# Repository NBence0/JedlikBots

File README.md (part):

# JedlikBots – Future Robotics Engineers from Győr, Hungary

Welcome to the official GitHub page of **JedlikBots**! 🎓🤖 We are the dedicated team of software development and robotics students from the Jedlik Ányos Technical School in Győr, Hungary. Our passion is to combine mechanical engineering, electronics, and software development to create innovative robotics solutions that address real-world problems. Our goal is to apply our acquired knowledge in national and international competitions and to inspire the next generation of engineers.

---

## 🚀 Our Main Project: ProBot X1 – The Next Generation of Competition Robots

The **ProBot X1** is our team's flagship project: a professional, modular robot platform specifically designed for the **WRO (World Robot Olympiad)** international competition series and other high-level technological challenges. During the robot's development, we use state-of-the-art technologies to create a truly competitive and versatile device.

<p align="center">
  
  <br>
  <em>The early but functional prototype of the ProBot X1 in its development environment.</em>
</p>

---

## 🔧 Technical Deep Dive: The Anatomy of ProBot X1

The ProBot X1 is not just a robot—it's a complex system designed and built with precision engineering. Below, we provide a detailed overview of the project's technical background.

### 1. Mechanical Design and Manufacturing Philosophy

The robot's physical frame and all mechanical components are entirely custom-designed. Our design philosophy centers around **modularity**, **robustness**, and **rapid iteration**.

*   **Design Software:** We create our models in professional CAD software, where every component is designed down to the smallest detail.
*   **Manufacturing Technology:** The parts are produced using 3D printing. This allows us to test new prototypes within days and flexibly adapt the robot's structure to the specific requirements of a given competition task.
*   **Material Selection:** We use PLA for prototypes and PETG or ABS for the final, high-stress components to ensure adequate strength and durability.

| Design in CAD Software (Video) | The Finished, Printed Components |
| :-------------------------------------------------------------------------------------------------------------------------------------------------------------------: | :-----------------------------------------------------------------------------------------------------------------: |
|  |  |
<p align="center"><em>On the left, the design process (click for video!), and on the right, the finished, printed components next to measurement instruments. The lattice structure provides optimal rigidity with minimal weight.</em></p>

### 2. Advanced Electronics and Custom-Designed PCB

The robot's brain and nervous system are comprised of a custom Printed Circuit Board (PCB) designed by us, located in the `Circuit/kicad/Robot fő nyák_v3/` folder. Our goal was to create a central board that integrates all control and sensor functions, minimizing wiring and maximizing reliability.

**The main functional blocks of the PCB:**

*   **Central Processing Unit (CPU):** The board hosts a **Raspberry Pi Compute Module 5 (CM5)**, which is responsible for computationally intensive tasks like machine vision and artificial intelligence.
*   **Real-Time Microcontroller (MCU):** An **ESP32-S3** microcontroller handles low-level, hardware-related control (motors, sensors), guaranteeing deterministic, real-time operation.
*   **Motor Control Subsystem:**
    *   Four **TMC5160** stepper motor drivers controlled via SPI for precise and silent movement. These drivers have advanced features like `StealthChop2™` for silent operation and `StallGuard2™` for sensorless homing.
    *   Multiple H-bridge outputs for driving DC motors and other actuators.
*   **Power Supply Unit (PSU):** A complex power supply providing multiple voltage levels (5V, 12V) and managing battery charging (`Battery-circuit.kicad_sch`). The system monitors the battery status and provides protection against overcharging and deep discharge.
*   **Sensor Interfaces:**
    *   **I²C Bus:** Multiple I²C devices, including a 9-axis IMU (BNO085) and an environmental sensor (BME280), are connected through an I²C multiplexer, allowing the simultaneous use of devices with the same address.
    *   **Analog-to-Digital Converter (ADC):** A high-resolution ADC (`ADS8688`) is responsible for the precise digitization of analog sensor signals (e.g., distance sensors).
*   **Peripherals:** USB hub, SD card reader, and numerous GPIO pins for modular expandability.

<p align="center">
  
  <br>
  <em>The "cable jungle"—an essential part of the prototyping phase, from which the final, clean PCB is born.</em>
</p>

### 3. Software Architecture and Intelligent Control

Hardware is only as good as the software that runs on it. The ProBot X1 is built on a sophisticated, two-tier software architecture.

#### High-Level Control (Raspberry Pi - Python)
The Python environment running on the Raspberry Pi is responsible for the robot's "intelligence."

*   **Machine Vision (OpenCV):** Our code in the `Camera/` folder implements a complete image processing pipeline:
    1.  **Image Acquisition:** Reading the frame from the camera.
    2.  **Preprocessing:** Converting the image to the HSV color space, which is more resistant to changes in lighting conditions. Applying Gaussian blur to reduce noise.
    3.  **Color and Shape Recognition:** Identifying relevant objects (e.g., colored blocks, lines) using color masking and contour detection.
    4.  **Data Extraction:** Determining the position, size, and orientation of objects in the camera's view.
*   **Decision-Making and Strategy:** Based on the processed data, the robot builds a state-space representation of its environment and plans its next moves to optimize score.

<p align="center">
  
  <br>
  <em>Click the image to watch the video! Based on the camera's image, the LED strip connected to the ESP32 lights up with the corresponding color.</em>
</p>

#### Low-Level Control and Firmware (ESP32 - C++)
The C++ firmware running on the ESP32 microcontroller, developed in the `PlatformIO` environment, ensures hard real-time operation.

*   **Responsibilities:** Receiving commands from the Raspberry Pi, precise stepping of motors, continuous collection and transmission of sensor data, and critical fault handling.
*   **Communication Protocol:** A custom, packet-based UART protocol connects the two brains. The protocol, developed in our `robot modells/v1.0/Full_uart_communication_logic_v2/` project, has the structure: `[START_BYTE, COMMAND_ID, PAYLOAD_LENGTH, PAYLOAD..., CHECKSUM]`. This structure guarantees data integrity and robust operation.

---

## 👥 Our Team

Meet the driving force behind JedlikBots, the students who power the project:

| Photo | Name | Role & Expertise |
| :---: | :--- | :--- |
|  | **Bence Nagy** | **Software Developer.** Specializes in sensor data processing, embedded systems programming, and 3D modeling. Bence is responsible for the robot's hardware abstraction layer and the design of its mechanical components. |
|  | **Nándor Schmidt** | **Electronics Designer & Firmware Developer.** The expert on the embedded systems behind the robots' "brains." He designs the PCBs and writes the low-level firmware, ensuring a perfect harmony between hardware and software. |
|  | **Bálint Buda** | **AI & Communications Developer.** Bálint is responsible for implementing machine learning algorithms and for the robot's wired and wireless communication. |

---

## 🏆 Competition Results and Goals

We are proud of our achievements so far and have set even bigger goals for ourselves.

*   **🥈 WRO 2025 Regional Final, Budapest - 2nd Place (May 2025)**
    *   We entered our first WRO competition with a LEGO Mindstorms EV3-based robot and achieved 2nd place in the Budapest regional final. This success qualified us for the national final but also highlighted the limitations of our current technology. With the new, professional ProBot X1, our goal is the World Final!

<p align="center">
  
  <br>
  <em>Click the image to watch our LEGO robot's competition run!</em>
</p>

---

## ❤️ Support the Engineers of the Future!

Developing the ProBot X1 and participating in international competitions require significant financial and technical resources. Our goal is to perform well at the WRO World Final, which requires building a world-class robot. This is where we need your help!

<p align="center">
  
  <br>
  <em>Click the image to see our workshop in action! This is where ideas and robots are born.</em>
</p>

### How You Can Help

1.  **With Equipment:** Modern components are essential for our project. Every single piece of donated equipment is a huge help. What we need most:
    *   **Microcontrollers:** Raspberry Pi (any version, including Compute Modules), STM-based boards.
    *   **Motors and Controllers:** Stepper motors, DC motors, servos, motor controllers.
    *   **Sensors:** Precision color and distance sensors, camera modules.
    *   **Materials:** 3D printer filament (PLA, PETG, 1.75 mm), breadboards, cables.
    *   **Measurement Tools:** Logic analyzer for debugging, oscilloscope.

2.  **With Professional Mentorship:** If you are an experienced engineer or developer and would like to share your knowledge, please contact us! A piece of good advice can be invaluable.

3.  **With Financial Support:** Your financial contribution can directly support the purchase of components and our travel to competitions.
### Contact
If you would like to contribute to our success, please write to us!
*   **Email:** nagy.bence1@students.jedlik.eu
*   **Phone:** +36 30 368 8136

---

## 🙏 Our Sponsors

We are deeply grateful to our current sponsors who believe in us and support our work!

<p align="center">

</p>

---

## 📂 Repository Contents

This repository documents the entire work of the JedlikBots team. You can find our projects in the following folders:

*   **`/Circuit/`**: Contains the designs for our custom Printed Circuit Boards (PCBs) in KiCad and Altium formats.
*   **`/Robot 3d/`**: 3D models of the robot's mechanical parts (STL, STP files).
*   **`/robot modells/`**: Various software modules and experimental programs that implement the robot's functions (PlatformIO projects).
*   **`/Camera/`**: Python scripts related to machine vision.
*   **`/media/`**: Images and videos of the robot, the team, and the competitions.
*   **`/web/`**: The source code for the team's official website.

**Thank you for your time! Follow our work and cheer for us at the next competition!**
# JedlikBots – A Jövő Robotikai Mérnökei Győrből

---
---

Üdvözlünk a **JedlikBots** hivatalos GitHub oldalán! 🎓🤖 Mi vagyunk a Győri Jedlik Ányos Technikum szoftverfejlesztő és robotika iránt elkötelezett diákcsapata. Szenvedélyünk a gépészet, az elektronika és a szoftverfejlesztés ötvözése, amellyel innovatív, valós problémákra választ adó robotikai megoldásokat hozunk létre. Célunk, hogy a megszerzett tudást hazai és nemzetközi versenyeken kamatoztassuk, és inspiráljuk a jövő mérnökgenerációját.

---

## 🚀 Fő Projektünk: ProBot X1 – A Versenyrobot Új Generációja

A **ProBot X1** a csapatunk zászlóshajója: egy professzionális, moduláris robotplatform, amelyet kifejezetten a **WRO (World Robot Olympiad)** nemzetközi versenysorozatra, valamint más magas szintű technológiai kihívásokra terveztünk. A robot fejlesztése során a legmodernebb technológiákat alkalmazzuk, hogy egy valóban versenyképes és sokoldalú eszközt hozzunk létre.

<p align="center">
  
  <br>
  <em>A ProBot X1 korai, de működő prototípusa a fejlesztői környezetben.</em>
</p>

---

## 🔧 Technikai Mélymerülés: A ProBot X1 Anatómája

A ProBot X1 nem csupán egy robot – egy komplex, precíziós mérnöki munkával megtervezett és épített rendszer. Az alábbiakban részletesen bemutatjuk a projekt műszaki hátterét.

### 1. Mechanikai Tervezés és Gyártásfilozófia

A robot fizikai váza és minden mechanikai eleme teljes mértékben egyedi tervezésű. A tervezési filozófiánk középpontjában a **modularitás**, a **robusztusság** és a **gyors iterálhatóság** áll.

*   **Tervező Szoftver:** A modelleket professzionális CAD szoftverekben készítjük, ahol minden alkatrészt a legapróbb részletekig megtervezünk.
*   **Gyártástechnológia:** Az alkatrészeket 3D nyomtatással állítjuk elő. Ez lehetővé teszi, hogy napok alatt új prototípusokat teszteljünk, és a robotot rugalmasan az adott versenyfeladat specifikus igényeihez igazítsuk.
*   **Anyagválasztás:** A prototípusokhoz PLA-t, a végleges, nagy igénybevételnek kitett alkatrészekhez pedig PETG-t vagy ABS-t használunk a megfelelő szilárdság és tartósság érdekében.

| Tervezés a CAD Szoftverben (Videó) | A Kész, Nyomtatott Alkatrészek |
| :-------------------------------------------------------------------------------------------------------------------------------------------------------------------: | :-----------------------------------------------------------------------------------------------------------------: |
|  |  |
<p align="center"><em>Bal oldalon a tervezési folyamat (kattints a videóért!), jobb oldalon a kész, nyomtatott alkatrészek a mérőműszerek mellett. A rácsszerkezet optimális merevséget biztosít minimális súly mellett.</em></p>

### 2. Fejlett Elektronika és Egyedi Tervezésű NyÁK

A robot agyát és idegrendszerét egy általunk, a `Circuit/kicad/Robot fő nyák_v3/` mappában tervezett egyedi nyomtatott áramkör (PCB) alkotja. A célunk egy olyan központi panel létrehozása volt, amely integrálja az összes vezérlési és szenzorikai funkciót, minimalizálva a kábelezést és maximalizálva a megbízhatóságot.

**A NyÁK fő funkcionális blokkjai:**

*   **Központi Feldolgozó Egység (CPU):** A panel fogad egy **Raspberry Pi Compute Module 5 (CM5)** kártyát, amely a nagy számítási igényű feladatokért, mint a gépi látás és a mesterséges intelligencia, felel.
*   **Valós Idejű Mikrokontroller (MCU):** Egy **ESP32-S3** mikrokontroller végzi a hardverközeli, alacsony szintű vezérlést (motorok, szenzorok), garantálva a determinisztikus, valós idejű működést.
*   **Motorvezérlő Alrendszer:**
    *   4 darab, SPI-on keresztül vezérelt **TMC5160** léptetőmotor-meghajtó a precíz és csendes mozgásért. Ezen meghajtók olyan fejlett funkciókkal bírnak, mint a `StealthChop2™` a hangtalan működésért és a `StallGuard2™` a szenzor nélküli végállás-érzékelésért.
    *   Több, H-híddal ellátott kimenet DC motorok és egyéb aktuátorok meghajtásához.
*   **Energiaellátás (PSU):** Egy komplex, több feszültségszintet (5V, 12V) biztosító tápegység, amely az akkumulátor töltését is menedzseli (`Battery-circuit.kicad_sch`). A rendszer figyeli az akkumulátor állapotát, és védelmet nyújt a túltöltés és mélykisülés ellen.
*   **Szenzor Interfészek:**
    *   **I²C Busz:** Több I²C eszköz, köztük egy 9 tengelyes IMU (BNO085) és egy környezeti szenzor (BME280) csatlakozik egy I²C multiplexeren keresztül, amely lehetővé teszi az azonos című eszközök egyidejű használatát.
    *   **Analóg-Digitális Konverter (ADC):** Egy nagy felbontású ADC (`ADS8688`) felel az analóg szenzorok (pl. távolságmérők) jeleinek precíz digitalizálásáért.
*   **Perifériák:** USB hub, SD kártya olvasó, és számos GPIO kivezetés a moduláris bővíthetőség érdekében.

<p align="center">
  
  <br>
  <em>A "kábel dzsungel" – a prototípus fázis elengedhetetlen része, amelyből a végleges, letisztult PCB megszületik.</em>
</p>

### 3. Szoftver Architektúra és Intelligens Vezérlés

A hardver csak annyit ér, amennyit a szoftver kihoz belőle. A ProBot X1 egy kifinomult, kétlépcsős szoftveres architektúrára épül.

#### Magas Szintű Vezérlés (Raspberry Pi - Python)
A Raspberry Pi-on futó Python környezet felel a robot "intelligenciájáért".

*   **Gépi Látás (OpenCV):** A `Camera/` mappában található kódjaink egy komplett képfeldolgozási folyamatot valósítanak meg:
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
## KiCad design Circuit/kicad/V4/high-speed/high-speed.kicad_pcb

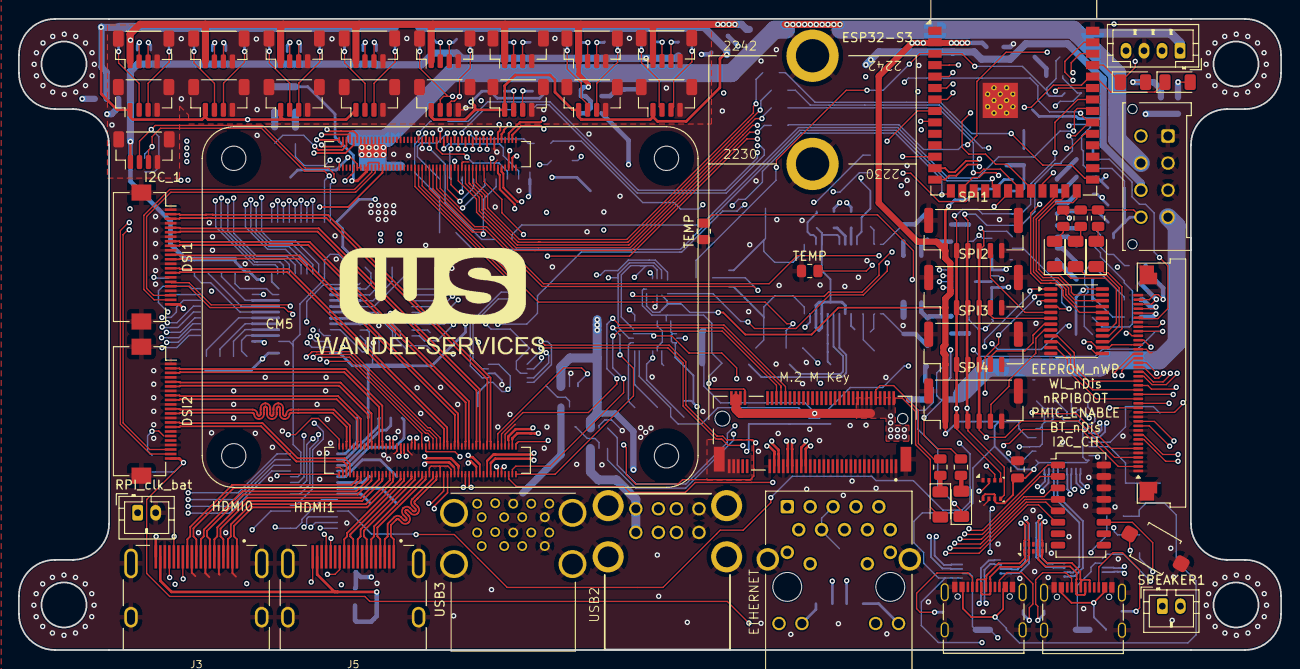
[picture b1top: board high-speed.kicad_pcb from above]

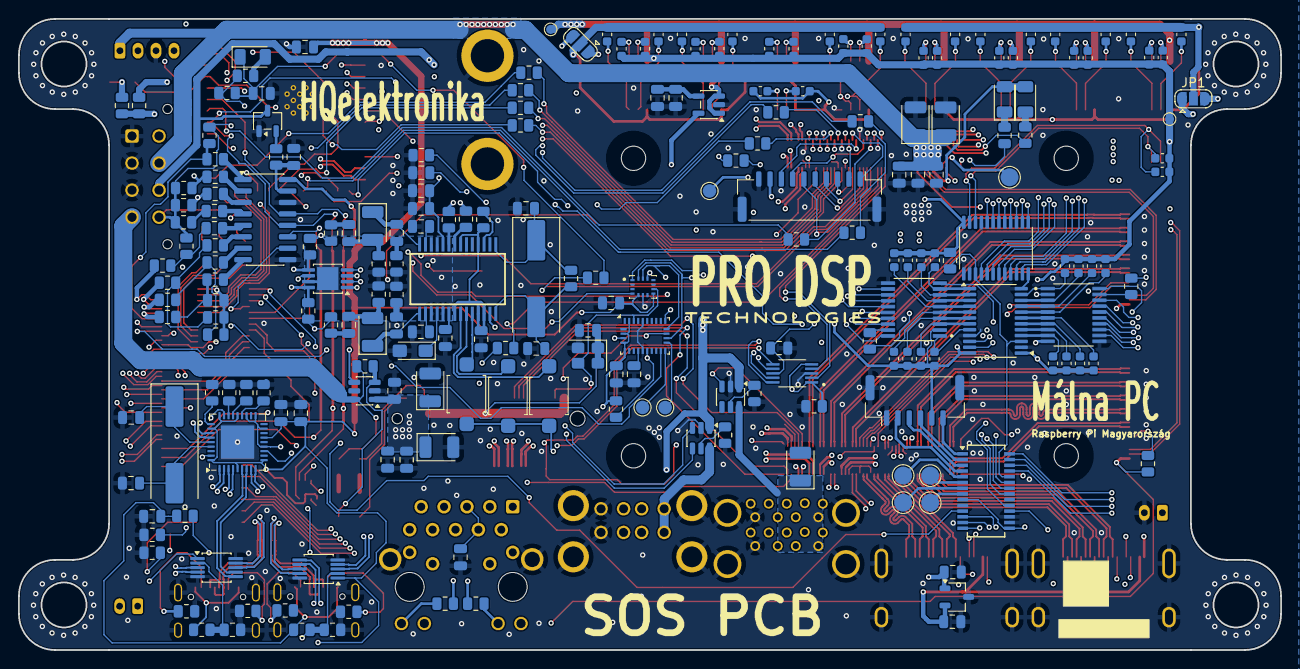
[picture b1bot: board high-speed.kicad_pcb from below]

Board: 6 copper layers, 140.0 x 70.0 mm, 274 parts (216 on the bottom side), 358 nets.

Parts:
C1, C2, C3, C7, C8, C13, C15, C18, C19, C21, C27, C36, C44, C59: 100nf; C_0805_2012Metric
C5, C6: 330pf; C_0805_2012Metric
C10, C66, C71: 100uF; CP_EIA-3528-21_Kemet-B
C14, C17, C24, C25, C28, C31, C61, C63, C64, C65, C67, C72: 1uf; C_0805_2012Metric
C16, C20, C58, C68, C69, C73: 22nf c0g; C_0805_2012Metric
C22, C23, C56, C57: 22pf; C_0805_2012Metric
C62: 10uF; CP_EIA-3216-18_Kemet-A_HandSolder
CM5: ComputeModule5-CM5; Raspberry-Pi-5-Compute-Module
CT1, CT2, CT3, CT4: 100uF; CP_EIA-3528-21_Kemet-B
D1, D2, D3, D4, D5, D6, D7, D8, D9, D10: LED; D_1206_3216Metric
DSI1: dsi; Hirose_FH12-22S-0.5SH_1x22-1MP_P0.50mm_Horizontal
DSI2: dsi1; Hirose_FH12-22S-0.5SH_1x22-1MP_P0.50mm_Horizontal
DSW1: SW_DIP_x08; SW_DIP_SPSTx08_Slide_Copal_CHS-08A_W5.08mm_P1.27mm_JPin
ESP32-S3: ESP32-S3-WROOM-1
I2C_0x70_1, I2C_0x70_2, I2C_0x70_3, I2C_0x70_4, I2C_0x70_5, I2C_0x70_6, I2C_0x70_7, I2C_0x70_8, I2C_0x71_1, I2C_0x71_2, I2C_0x71_3, I2C_0x71_4, I2C_0x71_5, I2C_0x71_6, I2C_0x71_7, I2C_0x71_8: Conn_01x04_Pin; JST_SH_BM04B-SRSS-TB_1x04-1MP_P1.00mm_Vertical
I2C_1: for default bus; JST_SH_BM04B-SRSS-TB_1x04-1MP_P1.00mm_Vertical
J1: Power Input; Molex_Micro-Fit_3.0_43045-0812_2x04_P3.00mm_Vertical
J2: from psu panel; Amphenol_F32Q-1A7x1-11040_1x40-1MP_P0.5mm_Horizontal
J3: HDMI0; EDAC 690-019-298-412
J5: HDMI1; EDAC 690-019-298-412
J6: RGB-BTN; JST_GH_BM06B-GHS-TBT_1x06-1MP_P1.25mm_Vertical
J7: MagJack-A70-112-331N126; TRJG0926HENL
J8: Fan; JST_PH_B4B-PH-K_1x04_P2.00mm_Vertical
J9: Conn_01x10_Socket; JST_GH_BM10B-GHS-TBT_1x10-1MP_P1.25mm_Vertical
J10: Bus_M.2_Socket_M; M.2 M Key socket
J11: USB_C_FLASH-RPI; USB_C_Receptacle_Palconn_UTC16-G
J12: USB_C_ESP; USB_C_Receptacle_Palconn_UTC16-G
JP1, JP3: SolderJumper_3_Open; SolderJumper-3_P1.3mm_Open_RoundedPad1.0x1.5mm
R1, R2, R3, R4: 0R; R_0805_2012Metric
R5, R30, R31: 2.2K; R_0805_2012Metric
R6, R40: 15K; R_0805_2012Metric
R7, R11, R15, R25, R93, R94, R96, R97, R98, R99, R102, R104, R106, R108, R110, R113, R116, R134, R136: 1K; R_0805_2012Metric
R8, R9: 470R; R_0805_2012Metric
R10, R12: 220R; R_0805_2012Metric
R13, R14, R16, R17, R18, R19, R20, R21, R119, R120: 22R; R_0805_2012Metric
R22, R23, R32, R33, R34, R85, R95, R101, R103, R105, R107, R109, R111, R114, R117, R124, R125, R128, R129, R130: 10K; R_0805_2012Metric
R24: 100R; R_0805_2012Metric
R26, R27, R28, R29: 5.1K; R_0805_2012Metric
R35: 12K; R_0805_2012Metric
R36, R37, R38, R39: 36K; R_0805_2012Metric
R41: 47K; R_0805_2012Metric
R42, R43, R44, R45, R46, R47, R48, R49, R50, R51, R52, R53, R54, R55, R56, R57, R58, R59, R60, R61, R62, R63, R64, R65, R66, R67, R68, R69, R70, R71, R72, R73, R74, R75, R76, R77, R78, R79, R80, R81, R82, R83, R84, R86, R87, R88, R89, R90, R91, R92: 2.2K; C_0603_1608Metric
R100: 10R; R_0805_2012Metric
R118: 1M; R_0805_2012Metric
R122: 1.5K; R_0805_2012Metric
R126, R132: 330R; R_0805_2012Metric
R127, R131: 16R; R_0805_2012Metric
R135: 10k; R_0805_2012Metric
R137, R138: 100k; R_0805_2012Metric
RPI_clk_bat: Battery_Cell; JST_PH_B2B-PH-K_1x02_P2.00mm_Vertical
SPEAKER1: Conn_01x02_Pin; JST_PH_B2B-PH-K_1x02_P2.00mm_Vertical
SPI1: spi1; JST_GH_BM06B-GHS-TBT_1x06-1MP_P1.25mm_Vertical
SPI2: spi2; JST_GH_BM06B-GHS-TBT_1x06-1MP_P1.25mm_Vertical
SPI3: spi3; JST_GH_BM06B-GHS-TBT_1x06-1MP_P1.25mm_Vertical
SPI4: spi4; JST_GH_BM06B-GHS-TBT_1x06-1MP_P1.25mm_Vertical
SW1, SW2, SW3, SW4: SW_Push; tact-smd sw
TEMP: 10K ntc; R_0805_2012Metric
TEMP#2: 10K ntc; R_0805_2012Metric
TP2: GPIO 16; TestPoint_Pad_D1.5mm
TP5: TestPoint; TestPoint_Pad_D2.0mm
TP9, TP10: TestPoint; TestPoint_Pad_D1.0mm
TP12: MCP_GPB_4; TestPoint_Pad_D2.0mm
TP13: MCP_GPB_5; TestPoint_Pad_D2.0mm
TP15: MCP_GPB_6; TestPoint_Pad_D2.0mm
TP16: MCP_GPB_7; TestPoint_Pad_D2.0mm
TP17: bno_sda; TestPoint_Pad_D1.5mm
TP18: bno_scl; TestPoint_Pad_D1.5mm
U1: TC1015-xCT; SOT-23-5
U2: RT9742SNGV; TSOT-23
U3, U13: AP22653W6; SOT-23-6
U6: AP22815AWU; SOT-23-6
U7: ASEK-32.768KHZ-L-R-T; Crystal_SMD_3225-4Pin_3.2x2.5mm
U8, U10: FSUSB42MUX; MSOP-10_3x3mm_P0.5mm
U9: TPD4EUSB30; USON-10_2.5x1.0mm_P0.5mm
U11: USB2514B-I/M2; QFN-36-1EP_6x6mm_P0.5mm_EP3.7x3.7mm
U14: TS5A23157DGSR; SOP50P490X110-10N
U15, U17: LSF0108PWR; SOP65P640X120-20N
U16, U18: TCA9548APWR; TSSOP-24_4.4x7.8mm_P0.65mm
U19: MCP23S17_SS; SSOP-28_3.9x9.9mm_P0.635mm
U20: CD74HC154M; TSSOP-24_4.4x7.8mm_P0.65mm
U21: XC6206P332MR; SOT-23-3
U22: MCP3208; SOIC-16_3.9x9.9mm_P1.27mm
U23: BME280; Bosch_LGA-8_2.5x2.5mm_P0.65mm_ClockwisePinNumbering
U24: BNO085; LGA-28_5.2x3.8mm_P0.5mm
U25: ICM-45686; IC_ICM-45686
U27: PCM2704CDBR; SSOP28
U28: TPA6203A1DGN; MSOP-8-1EP_3x3mm_P0.65mm_EP1.95x2.15mm_ThermalVias
USB2: ETHERNET; MOLEX_USB_67298-4090
USB3: USB3_A; MTCONN_UBAF30-D2011
Y1: 24MHz; Crystal_SMD_HC49-SD
Y2: 12MHz; Crystal_SMD_HC49-SD

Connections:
0NTC: R4.2, R117.2, R134.1
1NTC: R3.2, R114.2, R116.1
2NTC: R2.2, R111.2, R113.1
3NTC: R1.2, R109.2, R110.1
3V3_M.2: J1.4, R23.1, R24.1, U6.6 (IN)
32.768KHZ: J10.68 (SUSCLK), U7.3 (Out), U24.27 (XIN32), U25.9 (INT2/FSYNC/CLKIN)
/CM5_GPIO ( Ethernet, GPIOs)/+1.8v: CM5.88 (+1.8v_(Output)), CM5.90 (+1.8v_(Output)), TP5.1
/CM5_GPIO ( Ethernet, GPIOs)/+3.3v: CM5.78 (GPIO_VREF(1.8v/3.3v_Input)), CM5.84 (+3.3v_(Output)), CM5.86 (+3.3v_(Output)), D1.2 (A), D2.2 (A), DSI1.22, DSI2.22, J7.15 (LEDY_A), J7.17 (LEDG_A), J9.9, R5.1
/CM5_GPIO ( Ethernet, GPIOs)/BT_nDis: CM5.91 (BT_nDisable), DSW1.1
/CM5_GPIO ( Ethernet, GPIOs)/CAM_GPIO0: CM5.97 (CAM_GPIO0), DSI1.17
/CM5_GPIO ( Ethernet, GPIOs)/CAM_GPIO1: CM5.100 (CAM_GPIO1), DSI1.18
/CM5_GPIO ( Ethernet, GPIOs)/EEPROM_nWP: CM5.20 (EEPROM_nWP), DSW1.3
/CM5_GPIO ( Ethernet, GPIOs)/ETH_LEDG: CM5.17 (Ethernet_nLED2(3.3v)), R8.2
/CM5_GPIO ( Ethernet, GPIOs)/ETH_LEDY: CM5.15 (Ethernet_nLED3(3.3v)), R9.2
/CM5_GPIO ( Ethernet, GPIOs)/GPIO2: CM5.58 (GPIO2), U14.2 (NO1)
/CM5_GPIO ( Ethernet, GPIOs)/GPIO3: CM5.56 (GPIO3), U14.4 (NO2)
/CM5_GPIO ( Ethernet, GPIOs)/GPIO4: CM5.54 (GPIO4), R10.1
/CM5_GPIO ( Ethernet, GPIOs)/GPIO5: CM5.34 (GPIO5), R12.1
/CM5_GPIO ( Ethernet, GPIOs)/GPIO7: CM5.37 (GPIO7), J9.2
/CM5_GPIO ( Ethernet, GPIOs)/GPIO8: CM5.39 (GPIO8), J9.1
/CM5_GPIO ( Ethernet, GPIOs)/GPIO9: CM5.40 (GPIO9), J9.4
/CM5_GPIO ( Ethernet, GPIOs)/GPIO10: CM5.44 (GPIO10), J9.5
/CM5_GPIO ( Ethernet, GPIOs)/GPIO11: CM5.38 (GPIO11), J9.3
/CM5_GPIO ( Ethernet, GPIOs)/GPIO12: CM5.31 (GPIO12), R14.1
/CM5_GPIO ( Ethernet, GPIOs)/GPIO13: CM5.28 (GPIO13), R17.1
/CM5_GPIO ( Ethernet, GPIOs)/GPIO14: CM5.55 (GPIO14), R19.1
/CM5_GPIO ( Ethernet, GPIOs)/GPIO15: CM5.51 (GPIO15), R21.1
/CM5_GPIO ( Ethernet, GPIOs)/GPIO16: CM5.29 (GPIO16), TP2.1
/CM5_GPIO ( Ethernet, GPIOs)/GPIO17: CM5.50 (GPIO17), J9.6
/CM5_GPIO ( Ethernet, GPIOs)/GPIO18: CM5.49 (GPIO18), R20.1
/CM5_GPIO ( Ethernet, GPIOs)/GPIO19: CM5.26 (GPIO19), R18.1
/CM5_GPIO ( Ethernet, GPIOs)/GPIO20: CM5.27 (GPIO20), R16.1
/CM5_GPIO ( Ethernet, GPIOs)/GPIO21: CM5.25 (GPIO21), R13.1
/CM5_GPIO ( Ethernet, GPIOs)/GPIO24: CM5.45 (GPIO24), J9.7
/CM5_GPIO ( Ethernet, GPIOs)/GPIO25: CM5.41 (GPIO25), J9.8
/CM5_GPIO ( Ethernet, GPIOs)/GPIO26: CM5.24 (GPIO26), R11.1
/CM5_GPIO ( Ethernet, GPIOs)/GPIO27: CM5.48 (GPIO27), R136.1
/CM5_GPIO ( Ethernet, GPIOs)/ID_SC: CM5.35 (ID_SC), DSI2.20
/CM5_GPIO ( Ethernet, GPIOs)/ID_SD: CM5.36 (ID_SD), DSI2.21
/CM5_GPIO ( Ethernet, GPIOs)/PMIC_ENABLE: CM5.99 (PMIC_ENABLE), DSW1.2
/CM5_GPIO ( Ethernet, GPIOs)/PWM: CM5.19 (FAN_PWM), J8.2
/CM5_GPIO ( Ethernet, GPIOs)/PWR_BUT: CM5.92 (PWR_BUT), SW1.1
/CM5_GPIO ( Ethernet, GPIOs)/SCL0: CM5.80 (SCL0), DSI1.20
/CM5_GPIO ( Ethernet, GPIOs)/SDA0: CM5.82 (SDA0), DSI1.21
/CM5_GPIO ( Ethernet, GPIOs)/TACHO: CM5.16 (FAN_TACHO), J8.4
/CM5_GPIO ( Ethernet, GPIOs)/TRD0_N: CM5.10 (Ethernet_Pair0_N), J7.2 (TRD0-)
/CM5_GPIO ( Ethernet, GPIOs)/TRD0_P: CM5.12 (Ethernet_Pair0_P), J7.1 (TRD0+)
/CM5_GPIO ( Ethernet, GPIOs)/TRD1_N: CM5.6 (Ethernet_Pair1_N), J7.6 (TRD1-)
/CM5_GPIO ( Ethernet, GPIOs)/TRD1_P: CM5.4 (Ethernet_Pair1_P), J7.3 (TRD1+)
/CM5_GPIO ( Ethernet, GPIOs)/TRD2_N: CM5.9 (Ethernet_Pair2_N), J7.8 (TRD2-)
/CM5_GPIO ( Ethernet, GPIOs)/TRD2_P: CM5.11 (Ethernet_Pair2_P), J7.7 (TRD2+)
/CM5_GPIO ( Ethernet, GPIOs)/TRD3_N: CM5.5 (Ethernet_Pair3_N), J7.10 (TRD3-)
/CM5_GPIO ( Ethernet, GPIOs)/TRD3_P: CM5.3 (Ethernet_Pair3_P), J7.9 (TRD3+)
/CM5_GPIO ( Ethernet, GPIOs)/WL_nDis: CM5.89 (WiFi_nDisable), DSW1.5
/CM5_GPIO ( Ethernet, GPIOs)/nRPIBOOT: CM5.93 (nRPIBOOT), DSW1.4
/CM5_HighSpeed/DPHY0_C_N: CM5.127 (MIPI0_C_N), DSI1.8
/CM5_HighSpeed/DPHY0_C_P: CM5.129 (MIPI0_C_P), DSI1.9
/CM5_HighSpeed/DPHY0_D0_N: CM5.115 (MIPI0_D0_N), DSI1.2
/CM5_HighSpeed/DPHY0_D0_P: CM5.117 (MIPI0_D0_P), DSI1.3
/CM5_HighSpeed/DPHY0_D1_N: CM5.121 (MIPI0_D1_N), DSI1.5
/CM5_HighSpeed/DPHY0_D1_P: CM5.123 (MIPI0_D1_P), DSI1.6
/CM5_HighSpeed/DPHY0_D2_N: CM5.133 (MIPI0_D2_N), DSI1.11
/CM5_HighSpeed/DPHY0_D2_P: CM5.135 (MIPI0_D2_P), DSI1.12
/CM5_HighSpeed/DPHY0_D3_N: CM5.139 (MIPI0_D3_N), DSI1.14
/CM5_HighSpeed/DPHY0_D3_P: CM5.141 (MIPI0_D3_P), DSI1.15
/CM5_HighSpeed/DPHY1_C_N: CM5.187 (MIPI1_C_N), DSI2.8
/CM5_HighSpeed/DPHY1_C_P: CM5.189 (MIPI1_C_P), DSI2.9
/CM5_HighSpeed/DPHY1_D0_N: CM5.175 (MIPI1_D0_N), DSI2.2
/CM5_HighSpeed/DPHY1_D0_P: CM5.177 (MIPI1_D0_P), DSI2.3
/CM5_HighSpeed/DPHY1_D1_N: CM5.181 (MIPI1_D1_N), DSI2.5
/CM5_HighSpeed/DPHY1_D1_P: CM5.183 (MIPI1_D1_P), DSI2.6
/CM5_HighSpeed/DPHY1_D2_N: CM5.193 (MIPI1_D2_N), DSI2.11
/CM5_HighSpeed/DPHY1_D2_P: CM5.195 (MIPI1_D2_P), DSI2.12
/CM5_HighSpeed/DPHY1_D3_N: CM5.194 (MIPI1_D3_N), DSI2.14
/CM5_HighSpeed/DPHY1_D3_P: CM5.196 (MIPI1_D3_P), DSI2.15
/CM5_HighSpeed/HDMI0_CEC: CM5.151 (HDMI0_CEC), J3.13 (CEC)
/CM5_HighSpeed/HDMI0_CK_N: CM5.190 (HDMI0_CLK_N), J3.12 (CK-)
/CM5_HighSpeed/HDMI0_CK_P: CM5.188 (HDMI0_CLK_P), J3.10 (CK+)
/CM5_HighSpeed/HDMI0_D0_N: CM5.184 (HDMI0_TX0_N), J3.9 (D0-)
/CM5_HighSpeed/HDMI0_D0_P: CM5.182 (HDMI0_TX0_P), J3.7 (D0+)
/CM5_HighSpeed/HDMI0_D1_N: CM5.178 (HDMI0_TX1_N), J3.6 (D1-)
/CM5_HighSpeed/HDMI0_D1_P: CM5.176 (HDMI0_TX1_P), J3.4 (D1+)
/CM5_HighSpeed/HDMI0_D2_N: CM5.172 (HDMI0_TX2_N), J3.3 (D2-)
/CM5_HighSpeed/HDMI0_D2_P: CM5.170 (HDMI0_TX2_P), J3.1 (D2+)
/CM5_HighSpeed/HDMI0_HOTPLUG: CM5.153 (HDMI0_HOTPLUG), J3.19 (HPD/HEAC-)
/CM5_HighSpeed/HDMI0_SCL: CM5.200 (HDMI0_SCL), J3.15 (SCL)
/CM5_HighSpeed/HDMI0_SDA: CM5.199 (HDMI0_SDA), J3.16 (SDA)
/CM5_HighSpeed/HDMI1_CEC: CM5.149 (HDMI1_CEC), J5.13 (CEC)
/CM5_HighSpeed/HDMI1_CK_N: CM5.166 (HDMI1_CLK_N), J5.12 (CK-)
/CM5_HighSpeed/HDMI1_CK_P: CM5.164 (HDMI1_CLK_P), J5.10 (CK+)
/CM5_HighSpeed/HDMI1_D0_N: CM5.160 (HDMI1_TX0_N), J5.9 (D0-)
/CM5_HighSpeed/HDMI1_D0_P: CM5.158 (HDMI1_TX0_P), J5.7 (D0+)
/CM5_HighSpeed/HDMI1_D1_N: CM5.154 (HDMI1_TX1_N), J5.6 (D1-)
/CM5_HighSpeed/HDMI1_D1_P: CM5.152 (HDMI1_TX1_P), J5.4 (D1+)
/CM5_HighSpeed/HDMI1_D2_N: CM5.148 (HDMI1_TX2_N), J5.3 (D2-)
/CM5_HighSpeed/HDMI1_D2_P: CM5.146 (HDMI1_TX2_P), J5.1 (D2+)
/CM5_HighSpeed/HDMI1_HOTPLUG: CM5.143 (HDMI1_HOTPLUG), J5.19 (HPD/HEAC-)
/CM5_HighSpeed/HDMI1_SCL: CM5.147 (HDMI1_SCL), J5.15 (SCL)
/CM5_HighSpeed/HDMI1_SDA: CM5.145 (HDMI1_SDA), J5.16 (SDA)
/CM5_HighSpeed/HDMI_5v: C8.1, J3.18 (+5V), J5.18 (+5V), U2.2 (OUT)
/CM5_HighSpeed/PCIE_CLK_N: CM5.112 (PCIe_CLK_N), J10.53 (REFCLKn)
/CM5_HighSpeed/PCIE_CLK_P: CM5.110 (PCIe_CLK_P), J10.55 (REFCLKp)
/CM5_HighSpeed/PCIE_PWR_EN: CM5.106 (PCIE_PWR_EN), U6.4 (EN)
/CM5_HighSpeed/PCIE_RX_N: CM5.118 (PCIe_RX_N), J10.43 (PETp0)
/CM5_HighSpeed/PCIE_RX_P: CM5.116 (PCIe_RX_P), J10.41 (PETn0)
/CM5_HighSpeed/PCIE_TX_N: CM5.124 (PCIe_TX_N), J10.49 (PERp0)
/CM5_HighSpeed/PCIE_TX_P: CM5.122 (PCIe_TX_P), J10.47 (PERn0)
/CM5_HighSpeed/PCIE_nCLKREQ: CM5.102 (PCIe_nCLKREQ), J10.52 (~CLKREQ)
/CM5_HighSpeed/PCIE_nRST: CM5.109 (PCIe_nRST), J10.50 (~PERST)
/CM5_HighSpeed/PCIE_nWAKE: CM5.104 (PCIE_nWAKE), J10.54 (~PEWAKE)
/CM5_HighSpeed/USB2_N: CM5.103 (USB2_N), U8.4 (D_N)
/CM5_HighSpeed/USB2_P: CM5.105 (USB2_P), U8.3 (D_P)
/CM5_HighSpeed/USB3-0-D_N: CM5.136 (USB3-0-D_N), USB3.A2 (D-)
/CM5_HighSpeed/USB3-0-D_P: CM5.134 (USB3-0-D_P), USB3.A3 (D+)
/CM5_HighSpeed/USB3-0-RX_N: CM5.128 (USB3-0-RX_N), USB3.A6 (SSRX+)
/CM5_HighSpeed/USB3-0-RX_P: CM5.130 (USB3-0-RX_P), USB3.A5 (SSRX-)
/CM5_HighSpeed/USB3-0-TX_N: CM5.140 (USB3-0-TX_N), USB3.A9 (SSTX+)
/CM5_HighSpeed/USB3-0-TX_P: CM5.142 (USB3-0-TX_P), USB3.A8 (SSTX-)
/CM5_HighSpeed/USB3-1-D_N: CM5.165 (USB3-1-D_N), USB3.B2 (D-)
/CM5_HighSpeed/USB3-1-D_P: CM5.163 (USB3-1-D_P), USB3.B3 (D+)
/CM5_HighSpeed/USB3-1-RX_N: CM5.157 (USB3-1-RX_N), USB3.B6 (SSRX+)
/CM5_HighSpeed/USB3-1-RX_P: CM5.159 (USB3-1-RX_P), USB3.B5 (SSRX-)
/CM5_HighSpeed/USB3-1-TX_N: CM5.169 (USB3-1-TX_N), USB3.B9 (SSTX+)
/CM5_HighSpeed/USB3-1-TX_P: CM5.171 (USB3-1-TX_P), USB3.B8 (SSTX-)
/CM5_HighSpeed/USBOTG_ID: CM5.101 (USB_OTG_ID), R30.2, R32.1, U8.2 (SEL)
/CM5_HighSpeed/VBUS: C10.1, U3.6 (OUT), USB3.A1 (VBUS), USB3.B1 (VBUS)
/CM5_HighSpeed/VBUS_EN: CM5.111 (VBUS_EN), U3.3 (EN)
/I2C_CH: DSW1.6, R41.2, U14.1 (IN1), U14.5 (IN2), U19.23 (GPA2)
/I2C_MUX/ESP_I2C_SCL_sensors: ESP32-S3.17 (IO9), U14.7 (NC2)
/I2C_MUX/ESP_I2C_SDA_sensors: ESP32-S3.12 (IO8), U14.9 (NC1)
/I2C_MUX/I2C_SCL_sensors: I2C_1.3, J2.9, R75.2, U14.6 (COM2), U16.22 (SCL), U18.22 (SCL)
/I2C_MUX/I2C_SDA_sensors: I2C_1.2, J2.8, R64.2, U14.10 (COM1), U16.23 (SDA), U18.23 (SDA)
/I2C_RST: R85.2, U16.3 (~RESET), U18.3 (~RESET), U19.24 (GPA3)
/I2C_devices/I2C_LSF_Vsel_1: I2C_0x71_1.1, I2C_0x71_2.1, I2C_0x71_3.1, I2C_0x71_4.1, JP1.2 (C), R54.1, R56.1, R58.1, R61.1, R65.1, R67.1, R69.1, R71.1, R137.2, U15.10 (EN)
/I2C_devices/I2C_LSF_Vsel_2: I2C_0x71_5.1, I2C_0x71_6.1, I2C_0x71_7.1, I2C_0x71_8.1, JP3.2 (C), R55.1, R57.1, R59.1, R62.1, R66.1, R68.1, R70.1, R72.1, R138.2, U17.10 (EN)
/I2C_devices/SEN_1V8: JP1.3 (B), JP3.3 (B), U1.5 (VOUT)
/I2C_devices/Voltage_level_translation/In_SCL1: R76.2, U15.8 (A7), U16.5 (SC0)
/I2C_devices/Voltage_level_translation/In_SCL2: R78.2, U15.6 (A5), U16.7 (SC1)
/I2C_devices/Voltage_level_translation/In_SCL3: R80.2, U15.4 (A3), U16.9 (SC2)
/I2C_devices/Voltage_level_translation/In_SCL4: R82.2, U15.1 (A1), U16.11 (SC3)
/I2C_devices/Voltage_level_translation/In_SCL5: R84.2, U16.14 (SC4), U17.8 (A7)
/I2C_devices/Voltage_level_translation/In_SCL6: R87.2, U16.16 (SC5), U17.6 (A5)
/I2C_devices/Voltage_level_translation/In_SCL7: R89.2, U16.18 (SC6), U17.4 (A3)
/I2C_devices/Voltage_level_translation/In_SCL8: R91.2, U16.20 (SC7), U17.1 (A1)
/I2C_devices/Voltage_level_translation/In_SDA1: R77.2, U15.9 (A8), U16.4 (SD0)
/I2C_devices/Voltage_level_translation/In_SDA2: R79.2, U15.7 (A6), U16.6 (SD1)
/I2C_devices/Voltage_level_translation/In_SDA3: R81.2, U15.5 (A4), U16.8 (SD2)
/I2C_devices/Voltage_level_translation/In_SDA4: R83.2, U15.3 (A2), U16.10 (SD3)
/I2C_devices/Voltage_level_translation/In_SDA5: R86.2, U16.13 (SD4), U17.9 (A8)
/I2C_devices/Voltage_level_translation/In_SDA6: R88.2, U16.15 (SD5), U17.7 (A6)
/I2C_devices/Voltage_level_translation/In_SDA7: R90.2, U16.17 (SD6), U17.5 (A4)
/I2C_devices/Voltage_level_translation/In_SDA8: R92.2, U16.19 (SD7), U17.3 (A2)
/I2C_devices/Voltage_level_translation/SCL1: I2C_0x71_1.3, R69.2, U15.13 (B7)
/I2C_devices/Voltage_level_translation/SCL2: I2C_0x71_2.3, R65.2, U15.15 (B5)
/I2C_devices/Voltage_level_translation/SCL3: I2C_0x71_3.3, R58.2, U15.17 (B3)
/I2C_devices/Voltage_level_translation/SCL4: I2C_0x71_4.3, R54.2, U15.20 (B1)
/I2C_devices/Voltage_level_translation/SCL5: I2C_0x71_5.3, R70.2, U17.13 (B7)
/I2C_devices/Voltage_level_translation/SCL6: I2C_0x71_6.3, R66.2, U17.15 (B5)
/I2C_devices/Voltage_level_translation/SCL7: I2C_0x71_7.3, R59.2, U17.17 (B3)
/I2C_devices/Voltage_level_translation/SCL8: I2C_0x71_8.3, R55.2, U17.20 (B1)
/I2C_devices/Voltage_level_translation/SDA1: I2C_0x71_1.2, R71.2, U15.12 (B8)
/I2C_devices/Voltage_level_translation/SDA2: I2C_0x71_2.2, R67.2, U15.14 (B6)
/I2C_devices/Voltage_level_translation/SDA3: I2C_0x71_3.2, R61.2, U15.16 (B4)
/I2C_devices/Voltage_level_translation/SDA4: I2C_0x71_4.2, R56.2, U15.18 (B2)
/I2C_devices/Voltage_level_translation/SDA5: I2C_0x71_5.2, R72.2, U17.12 (B8)
/I2C_devices/Voltage_level_translation/SDA6: I2C_0x71_6.2, R68.2, U17.14 (B6)
/I2C_devices/Voltage_level_translation/SDA7: I2C_0x71_7.2, R62.2, U17.16 (B4)
/I2C_devices/Voltage_level_translation/SDA8: I2C_0x71_8.2, R57.2, U17.18 (B2)
/I2C_devices/multiplexer_0x70/SCL1: I2C_0x70_1.3, R49.2, U18.10 (SD3)
/I2C_devices/multiplexer_0x70/SCL2: I2C_0x70_2.3, R47.2, U18.8 (SD2)
/I2C_devices/multiplexer_0x70/SCL3: I2C_0x70_3.3, R45.2, U18.6 (SD1)
/I2C_devices/multiplexer_0x70/SCL4: I2C_0x70_4.3, R43.2, U18.4 (SD0)
/I2C_devices/multiplexer_0x70/SCL5: I2C_0x70_5.3, R50.2, U18.14 (SC4)
/I2C_devices/multiplexer_0x70/SCL6: I2C_0x70_6.3, R52.2, U18.16 (SC5)
/I2C_devices/multiplexer_0x70/SCL7: I2C_0x70_7.3, R60.2, U18.18 (SC6)
/I2C_devices/multiplexer_0x70/SCL8: I2C_0x70_8.3, R73.2, U18.20 (SC7)
/I2C_devices/multiplexer_0x70/SDA1: I2C_0x70_1.2, R48.2, U18.11 (SC3)
/I2C_devices/multiplexer_0x70/SDA2: I2C_0x70_2.2, R46.2, U18.9 (SC2)
/I2C_devices/multiplexer_0x70/SDA3: I2C_0x70_3.2, R44.2, U18.7 (SC1)
/I2C_devices/multiplexer_0x70/SDA4: I2C_0x70_4.2, R42.2, U18.5 (SC0)
/I2C_devices/multiplexer_0x70/SDA5: I2C_0x70_5.2, R51.2, U18.13 (SD4)
/I2C_devices/multiplexer_0x70/SDA6: I2C_0x70_6.2, R53.2, U18.15 (SD5)
/I2C_devices/multiplexer_0x70/SDA7: I2C_0x70_7.2, R63.2, U18.17 (SD6)
/I2C_devices/multiplexer_0x70/SDA8: I2C_0x70_8.2, R74.2, U18.19 (SD7)
/INA226_ALERT: CM5.30 (GPIO6), J2.33
/INA226_SCL: CM5.46 (GPIO22), J2.12
/INA226_SDA: CM5.47 (GPIO23), J2.11
/PCIe-M2/M2_3v3: C17.1, C18.1, C19.1, C20.1, CT3.1, CT4.1, D4.2 (A), J10.2 (3.3V), J10.4 (3.3V), J10.12 (3.3V), J10.14 (3.3V), J10.16 (3.3V), J10.18 (3.3V), J10.70 (3.3V), J10.72 (3.3V), J10.74 (3.3V), U6.1 (OUT), U7.1 (EN), U7.4 (VDD)
/Real-time-controll/AIN1: J2.25, U19.25 (GPA4)
/Real-time-controll/AIN2: J2.24, U19.26 (GPA5)
/Real-time-controll/BIN1: J2.23, U19.27 (GPA6)
/Real-time-controll/BIN2: J2.22, U19.28 (GPA7)
/Real-time-controll/BNO_BOOT: U19.22 (GPA1), U24.4 (BOOTN)
/Real-time-controll/BNO_INT: ESP32-S3.8 (IO15), U24.14 (H_INTN)
/Real-time-controll/BNO_RST: R135.1, U19.21 (GPA0), U24.11 (NRST)
/Real-time-controll/BTN_ACT: J6.6, U19.1 (GPB0)
/Real-time-controll/BTN_B: J6.4, U19.2 (GPB1)
/Real-time-controll/BTN_G: J6.3, U19.3 (GPB2)
/Real-time-controll/BTN_R: J6.2, U19.4 (GPB3)
/Real-time-controll/CS_S_A0: ESP32-S3.26 (IO45), U20.23 (A0)
/Real-time-controll/CS_S_A1: ESP32-S3.25 (IO48), U20.22 (A1)
/Real-time-controll/CS_S_A2: ESP32-S3.24 (IO47), U20.21 (A2)
/Real-time-controll/CS_S_A3: ESP32-S3.16 (IO46), U20.20 (A3)
/Real-time-controll/ESP_RST: C24.1, D8.1 (K), ESP32-S3.3 (EN), R95.1, R136.2
/Real-time-controll/ESP_UART_RX: D5.1 (K), ESP32-S3.36 (RXD0), R10.2
/Real-time-controll/ESP_UART_TX: D6.1 (K), ESP32-S3.37 (TXD0), R12.2
/Real-time-controll/ICM_INT: ESP32-S3.9 (IO16), U25.4 (INT1/INT)
/Real-time-controll/M1_CS: J2.21, U20.9 (~Y8)
/Real-time-controll/M1_step: ESP32-S3.4 (IO4), J2.20
/Real-time-controll/M2_CS: J2.19, U20.10 (~Y9)
/Real-time-controll/M2_step: ESP32-S3.5 (IO5), J2.18
/Real-time-controll/M3_CS: J2.17, U20.11 (~Y10)
/Real-time-controll/M3_step: ESP32-S3.6 (IO6), J2.16
/Real-time-controll/M4_CS: J2.15, U20.13 (~Y11)
/Real-time-controll/M4_step: ESP32-S3.7 (IO7), J2.14
/Real-time-controll/MCP_CS: J2.29, U19.11 (~CS), U20.14 (~Y12)
/Real-time-controll/MCP_IntB: ESP32-S3.35 (IO42), U19.19 (INTB)
/Real-time-controll/MCP_RST: ESP32-S3.15 (IO3), J2.30, U19.18 (~RESET)
/Real-time-controll/PWMA: ESP32-S3.39 (IO1), J2.27
/Real-time-controll/PWMB: ESP32-S3.38 (IO2), J2.26
/Real-time-controll/RPI-ESP_INT: ESP32-S3.27 (IO0), R11.2
/Real-time-controll/RPI_CS: ESP32-S3.22 (IO14), R14.2
/Real-time-controll/RPI_MISO: ESP32-S3.20 (IO12), R19.2
/Real-time-controll/RPI_MOSI: ESP32-S3.21 (IO13), R17.2
/Real-time-controll/RPI_SPI_CLK: ESP32-S3.19 (IO11), R21.2
/Real-time-controll/SENSOR_CS: ESP32-S3.33 (IO40), R20.2
/Real-time-controll/SPI_CS_1: U20.1 (~Y0), U25.12 (AP_CS)
/Real-time-controll/SPI_CS_2: U20.2 (~Y1), U24.18 (H_CSN)
/Real-time-controll/SPI_CS_3: U20.3 (~Y2), U23.2 (CSB)
/Real-time-controll/SPI_CS_4: U20.4 (~Y3), U22.10 (~CS/SHDN)
/Real-time-controll/SPI_CS_5: SPI4.5, U20.8 (~Y7)
/Real-time-controll/SPI_CS_6: SPI3.5, U20.7 (~Y6)
/Real-time-controll/SPI_CS_7: SPI2.5, U20.6 (~Y5)
/Real-time-controll/SPI_CS_8: SPI1.5, U20.5 (~Y4)
/Real-time-controll/SPI_DIAG0: D7.1 (K), U20.15 (~Y13)
/Real-time-controll/SPI_DIAG1: D9.1 (K), U20.16 (~Y14)
/Real-time-controll/SPI_DIAG2: D10.1 (K), U20.17 (~Y15)
/Real-time-controll/WS_2802B_DATA: ESP32-S3.23 (IO21), J2.31
/SENSOR_MISO: ESP32-S3.32 (IO39), J2.2, R16.2, SPI1.3, SPI2.3, SPI3.3, SPI4.3, U19.13 (SI), U22.12 (Dout), U23.5 (SDO), U24.20 (H_SDA/MISO/TX), U25.1 (AP_SDO/AP_AD0)
/SENSOR_MOSI: ESP32-S3.31 (IO38), J2.4, R18.2, SPI1.4, SPI2.4, SPI3.4, SPI4.4, U19.14 (SO), U22.11 (Din), U23.3 (SDI), U24.17 (H_SA0/MOSI), U25.14 (AP_SDA/AP_SDIO/AP_SDI)
/SENSOR_SPI_CLK: ESP32-S3.34 (IO41), J2.6, R13.2, SPI1.2, SPI2.2, SPI3.2, SPI4.2, U19.12 (SCK), U22.13 (CLK), U23.4 (SCK), U24.19 (H_SCL/SCLK/RX), U25.13 (AP_SCL/AP_SCLK)
/USB2-HUB/HD1_N: U11.1 (USBDM_DN1/PRT_DIS_M1), USB2.2 (D-`)
/USB2-HUB/HD1_P: U11.2 (USBDP_DN1/PRT_DIS_P1), USB2.3 (D+`)
/USB2-HUB/HD2_N: U11.3 (USBDM_DN2/PRT_DIS_M2), USB2.6 (D-)
/USB2-HUB/HD2_P: U11.4 (USBDP_DN2/PRT_DIS_P2), USB2.7 (D+)
/USB2-HUB/HD3_N: U10.6 (HSD0_M), U11.6 (USBDM_DN3/PRT_DIS_M3)
/USB2-HUB/HD3_P: U10.7 (HSD0_P), U11.7 (USBDP_DN3/PRT_DIS_P3)
/USB2-HUB/HD4_N: R120.1, U11.8 (USBDM_DN4/PRT_DIS_M4)
/USB2-HUB/HD4_P: R119.1, U11.9 (USBDP_DN4/PRT_DIS_P4)
/USB2-HUB/PWR1: U11.12 (PRTPWR1/BC_EN1), U13.3 (EN)
/USB2-HUB/USB-AUDIO/BYPASS: C68.1, U28.2 (BYPASS)
/USB2-HUB/USB-AUDIO/Vdd: C61.1, R122.2, U27.4 (PSEL), U27.7 (VDD), U27.21 (HOST), U27.25 (TEST1), U27.26 (TEST0)
/USB2-HUB/USBD_N: J11.A7 (D-), J11.B7 (D-), U8.8 (HSD1_M), U9.1 (D1+), U9.10
/USB2-HUB/USBD_P: J11.A6 (D+), J11.B6 (D+), U8.9 (HSD1_P), U9.2 (D1-), U9.9
/USB2-HUB/USBF_N: J12.A7 (D-), J12.B7 (D-), U9.4 (D2+), U9.7, U10.8 (HSD1_M)
/USB2-HUB/USBF_P: J12.A6 (D+), J12.B6 (D+), U9.5 (D2-), U9.6, U10.9 (HSD1_P)
/USB2-HUB/USBH_N: U8.6 (HSD0_M), U11.30 (USBDM_UP)
/USB2-HUB/USBH_P: U8.7 (HSD0_P), U11.31 (USBDP_UP)
/USB2-HUB/VBUS: U13.6 (OUT), USB2.1 (VBUS`), USB2.5 (VBUS)
/USB2-HUB/nEXTRST: C21.2, J11.A4 (VBUS), J11.A9 (VBUS), J11.B4 (VBUS), J11.B9 (VBUS), R30.1, R34.1
/USB2-HUB/nOCS1: U11.13 (OCS_N1), U11.17 (OCS_N2), U11.19 (OCS_N3), U11.21 (OCS_N4), U13.4 (nFault)
/esp_usbD+: ESP32-S3.14 (USB_D+), U10.3 (D_P)
/esp_usbD-: ESP32-S3.13 (USB_D-), U10.4 (D_N)
ESP_3v3: C1.2, C2.2, C3.2, C25.2, C27.1, C28.1, C31.2, ESP32-S3.2 (3V3), I2C_0x70_1.1, I2C_0x70_2.1, I2C_0x70_3.1, I2C_0x70_4.1, I2C_0x70_5.1, I2C_0x70_6.1, I2C_0x70_7.1, I2C_0x70_8.1, I2C_1.1, J1.8, J6.5, R42.1, R43.1, R44.1, R45.1, R46.1, R47.1, R48.1, R49.1, R50.1, R51.1, R52.1, R53.1, R60.1, R63.1, R64.1, R73.1, R74.1, R75.1, R76.1, R77.1, R78.1, R79.1, R80.1, R81.1, R82.1, R83.1, R84.1, R85.1, R86.1, R87.1, R88.1, R89.1, R90.1, R91.1, R92.1, R93.2, R94.2, R95.2, R96.2, R97.2, R98.2, R99.2, R101.1, R103.1, R105.1, R107.1, R109.1, R111.1, R114.1, R117.1, R135.2, SPI1.1, SPI2.1, SPI3.1, SPI4.1, TP9.1, TP10.1, U1.1 (VIN), U1.3 (~SHDN), U8.1 (VCC), U10.1 (VCC), U11.5 (VDDA33), U11.10 (VDDA33), U11.15 (VDD33), U11.23 (VDD33), U11.27 (VBUS_DET), U11.29 (VDDA33), U11.36 (VDDA33), U14.8 (V+), U15.2 (VREF_A), U16.1 (A0), U16.24 (VCC), U17.2 (VREF_A), U18.24 (VCC), U19.9 (VDD), U19.15 (A0), U20.24 (VCC), U22.16 (Vdd), U23.6 (VDDIO), U23.8 (VDD), U24.3 (VDD), U24.5 (PS1), U24.6 (PS0/WAKE), U24.28 (VDDIO), U25.5 (VDDIO), U25.8 (VDD)
ESP_5v: J1.7, JP1.1 (A), JP3.1 (A), U21.3 (VI)
GND: C1.1, C2.1, C3.1, C5.1, C6.1, C7.2, C8.2, C10.2, C13.2, C14.2, C15.2, C16.2, C17.2, C18.2, C19.2, C20.2, C21.1, C22.1, C23.1, C24.2, C25.1, C27.2, C28.2, C31.1, C36.2, C44.2, C56.2, C57.2, C58.2, C59.2, C61.2, C62.2, C63.2, C64.2, C65.2, C68.2, CM5.1 (GND), CM5.2 (GND), CM5.7 (GND), CM5.8 (GND), CM5.13 (GND), CM5.14 (GND), CM5.22 (GND), CM5.23 (GND), CM5.32 (GND), CM5.33 (GND), CM5.42 (GND), CM5.43 (GND), CM5.52 (GND), CM5.53 (GND), CM5.59 (GND), CM5.60 (GND), CM5.65 (GND), CM5.66 (GND), CM5.71 (GND), CM5.74 (GND), CM5.98 (GND), CM5.107 (GND), CM5.108 (GND), CM5.113 (GND), CM5.114 (GND), CM5.119 (GND), CM5.120 (GND), CM5.125 (GND), CM5.126 (GND), CM5.131 (GND), CM5.132 (GND), CM5.137 (GND), CM5.138 (GND), CM5.144 (GND), CM5.150 (GND), CM5.155 (GND), CM5.156 (GND), CM5.161 (GND), CM5.162 (GND), CM5.167 (GND), CM5.168 (GND), CM5.173 (GND), CM5.174 (GND), CM5.179 (GND), CM5.180 (GND), CM5.185 (GND), CM5.186 (GND), CM5.191 (GND), CM5.192 (GND), CM5.197 (GND), CM5.198 (GND), CT1.2, CT2.2, CT3.2, CT4.2, DSI1.1, DSI1.4, DSI1.7, DSI1.10, DSI1.13, DSI1.16, DSI1.19, DSI1.MP (Pin_22), DSI2.1, DSI2.4, DSI2.7, DSI2.10, DSI2.13, DSI2.16, DSI2.19, DSI2.MP (Pin_22), DSW1.12, DSW1.13, DSW1.14, DSW1.15, DSW1.16, ESP32-S3.1 (GND), ESP32-S3.40 (GND), ESP32-S3.41 (GND), I2C_0x70_1.4, I2C_0x70_2.4, I2C_0x70_3.4, I2C_0x70_4.4, I2C_0x70_5.4, I2C_0x70_6.4, I2C_0x70_7.4, I2C_0x70_8.4, I2C_0x71_1.4, I2C_0x71_2.4, I2C_0x71_3.4, I2C_0x71_4.4, I2C_0x71_5.4, I2C_0x71_6.4, I2C_0x71_7.4, I2C_0x71_8.4, I2C_1.4, J1.1, J1.2, J1.3, J2.1, J2.3, J2.5, J2.7, J2.10, J2.13, J2.28, J2.34, J2.40, J2.MP (MountPin), J3.2 (D2S), J3.5 (D1S), J3.8 (D0S), J3.11 (CKS), J3.17 (GND), J3.SH1 (SH), J3.SH2 (SH), J3.SH3 (SH), J3.SH4 (SH), J5.2 (D2S), J5.5 (D1S), J5.8 (D0S), J5.11 (CKS), J5.17 (GND), J5.SH1 (SH), J5.SH2 (SH), J5.SH3 (SH), J5.SH4 (SH), J6.1, J6.MP (MountPin), J7.19 (SHIELD), J7.20 (SHIELD), J8.3, J9.10, J9.MP (MountPin), J10.1 (GND), J10.3 (GND), J10.9 (GND), J10.15 (GND), J10.21 (GND), J10.27 (GND), J10.33 (GND), J10.39 (GND), J10.45 (GND), J10.51 (GND), J10.57 (GND), J10.71 (GND), J10.73 (GND), J10.75 (GND), J10.M1 (GND2230), J10.M2 (GND2242), J10.S1, J10.S2, J11.A1 (GND), J11.A12 (GND), J11.B1 (GND), J11.B12 (GND), J11.S1 (SHIELD), J12.A1 (GND), J12.A12 (GND), J12.B1 (GND), J12.B12 (GND), J12.S1 (SHIELD), R6.2, R22.2, R26.1, R27.1, R28.1, R29.1, R32.2, R33.2, R35.1, R36.2, R37.2, R38.2, R39.2, R40.2, R41.1, R126.1, R127.1, R130.2, R131.1, R132.1, RPI_clk_bat.2 (-), SPI1.6, SPI1.MP (MountPin), SPI2.6, SPI2.MP (MountPin), SPI3.6, SPI3.MP (MountPin), SPI4.6, SPI4.MP (MountPin), SW1.2, TEMP.1, TEMP#2.1, U1.2 (GND), U2.3 (GND), U3.2 (GND), U6.2 (GND), U7.2 (GND), U8.5 (GND), U8.10 (nOE), U9.3 (GND), U9.8 (GND), U10.5 (GND), U10.10 (nOE), U11.37 (VSS), U13.2 (GND), U14.3 (GND), U15.11 (GND), U16.2 (A1), U16.12 (GND), U16.21 (A2), U17.11 (GND), U18.1 (A0), U18.2 (A1), U18.12 (GND), U18.21 (A2), U19.10 (VSS), U19.16 (A1), U19.17 (A2), U20.12 (GND), U20.18 (E1), U20.19 (E2), U21.1 (GND), U22.9 (DGND), U22.14 (AGND), U23.1 (GND), U23.7 (GND), U24.2 (GND), U24.10 (CLKSEL0), U24.25 (GNDIO), U25.6 (GND), U27.6 (DGND), U27.11 (ZGND), U27.12 (AGNDL), U27.17 (AGNDR), U27.19 (PGND), U28.7 (GND), U28.9 (GND), USB2.4 (GND`)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
unnamed: CM5.76 (VBAT), RPI_clk_bat.1 (+)
unnamed: C13.1, J7.4 (CT), J7.5 (CT)
unnamed: C66.2, C67.2, R126.2
unnamed: C67.1, R124.1
unnamed: C69.2, R127.2
unnamed: C71.2, C72.2, R132.2
unnamed: C72.1, R128.1
unnamed: C73.2, R131.2
unnamed: D1.1 (K), R7.1
unnamed: D2.1 (K), R15.1
unnamed: D3.2 (A), R24.2
unnamed: D3.1 (K), R23.2, U6.3 (FLG)
unnamed: D4.1 (K), R25.1
unnamed: D5.2 (A), R93.1
unnamed: D6.2 (A), R94.1
unnamed: D7.2 (A), R97.1
unnamed: D8.2 (A), R96.1
unnamed: D9.2 (A), R98.1
unnamed: D10.2 (A), R99.1
unnamed: DSI2.17, R5.2
unnamed: DSW1.11, R22.1
unnamed: J2.36, R4.1
unnamed: J2.37, R3.1
unnamed: J2.38, R2.1
unnamed: J2.39, R1.1
unnamed: J7.18 (LEDG_K), R9.1
unnamed: J7.16 (LEDY_K), R8.1
unnamed: J10.10 (DAS/~DSS/~LED1), R25.2
unnamed: J11.A5 (CC1), R26.2
unnamed: J11.B5 (CC2), R28.2
unnamed: J12.A5 (CC1), R27.2
unnamed: J12.B5 (CC2), R29.2
unnamed: J12.A4 (VBUS), J12.A9 (VBUS), J12.B4 (VBUS), J12.B9 (VBUS), R31.1
unnamed: CM5.21 (LED_nACT), R7.2
unnamed: CM5.95 (LED_nPWR), R15.2
unnamed: R103.2, R104.1, TEMP.2
unnamed: R105.2, R106.1, TEMP#2.2
unnamed: R107.2, R108.1
unnamed: R129.2, SPEAKER1.1, U28.8 (V_{O-})
unnamed: R125.2, SPEAKER1.2, U28.5 (V_{O+})
unnamed: C5.2, C6.2, U1.4 (Bypass)
unnamed: R6.1, U3.5 (ILIM)
unnamed: R31.2, R33.1, U10.2 (SEL)
unnamed: R39.1, U11.25 (HS_IND/CFG_SEL1)
unnamed: R35.2, U11.35 (RBIAS)
unnamed: R34.2, U11.26 (RESET_N)
unnamed: R36.1, U11.24 (SCL/SMBCLK/CFG_SEL0)
unnamed: R37.1, U11.22 (SDA/SMBDATA/NON_REM1)
unnamed: R38.1, U11.28 (SUSP_IND/LOCAL_PWR/NON_REM0)
unnamed: C22.2, U11.33 (XTALIN/CLKIN), Y1.2
unnamed: C23.2, U11.32 (XTALOUT), Y1.1
unnamed: R40.1, U13.5 (ILIM)
unnamed: R137.1, U15.19 (VREF_B)
unnamed: R138.1, U17.19 (VREF_B)
unnamed: TP12.1, U19.5 (GPB4)
unnamed: TP13.1, U19.6 (GPB5)
unnamed: TP15.1, U19.7 (GPB6)
unnamed: TP16.1, U19.8 (GPB7)
unnamed: R100.2, U21.2 (VO)
unnamed: R102.2, U22.1 (CH0)
unnamed: R104.2, U22.2 (CH1)
unnamed: R106.2, U22.3 (CH2)
unnamed: R108.2, U22.4 (CH3)
unnamed: R110.2, U22.5 (CH4)
unnamed: R113.2, U22.6 (CH5)
unnamed: R116.2, U22.7 (CH6)
unnamed: R134.2, U22.8 (CH7)
unnamed: C36.1, R100.1, U22.15 (Vref)
unnamed: C44.1, U24.9 (CAP)
unnamed: TP18.1, U24.15 (S_SCL)
unnamed: TP17.1, U24.16 (S_SDA)
unnamed: R119.2, U27.9 (D+)
unnamed: R120.2, U27.8 (D-)
unnamed: R122.1, U27.3 (DT)
unnamed: SW2.2, U27.22 (HID0/MS)
unnamed: SW3.2, U27.23 (HID1/MC)
unnamed: SW4.2, U27.24 (HID2/MD)
unnamed: C65.1, U27.13 (VCCL)
unnamed: C63.1, U27.20 (VCCP)
unnamed: C64.1, U27.16 (VCCR)
unnamed: C62.1, U27.18 (VCOM)
unnamed: C66.1, C69.1, U27.14 (VOUTL)
unnamed: C71.1, C73.1, U27.15 (VOUTR)
unnamed: C57.1, R118.2, U27.28 (XTI), Y2.2
unnamed: C56.1, R118.1, U27.1 (XTO), Y2.1
unnamed: SW2.1, SW3.1, SW4.1, U27.27 (~SSPND)
unnamed: R128.2, R129.1, U28.3 (IN+)
unnamed: R124.2, R125.1, U28.4 (IN-)
PSU-NTC: J2.35, R101.2, R102.1
RPI_5v: C14.1, C15.1, C16.1, CM5.77 (+5v_(Input)), CM5.79 (+5v_(Input)), CM5.81 (+5v_(Input)), CM5.83 (+5v_(Input)), CM5.85 (+5v_(Input)), CM5.87 (+5v_(Input)), CT1.1, CT2.1, J1.6, J8.1
TPA_ON: J2.32, R130.1, U28.1 (~SHUTDOWN)
USB_5v: C7.1, C58.1, C59.1, J1.5, U2.1 (IN), U3.1 (IN), U13.1 (IN), U27.10 (VBUS), U28.6 (V_{DD})
